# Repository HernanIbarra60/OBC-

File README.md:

# OBC-
This project is an On-Board Computer (OBC) for a CubeSat. Its main core is an STM32F4 microcontroller.

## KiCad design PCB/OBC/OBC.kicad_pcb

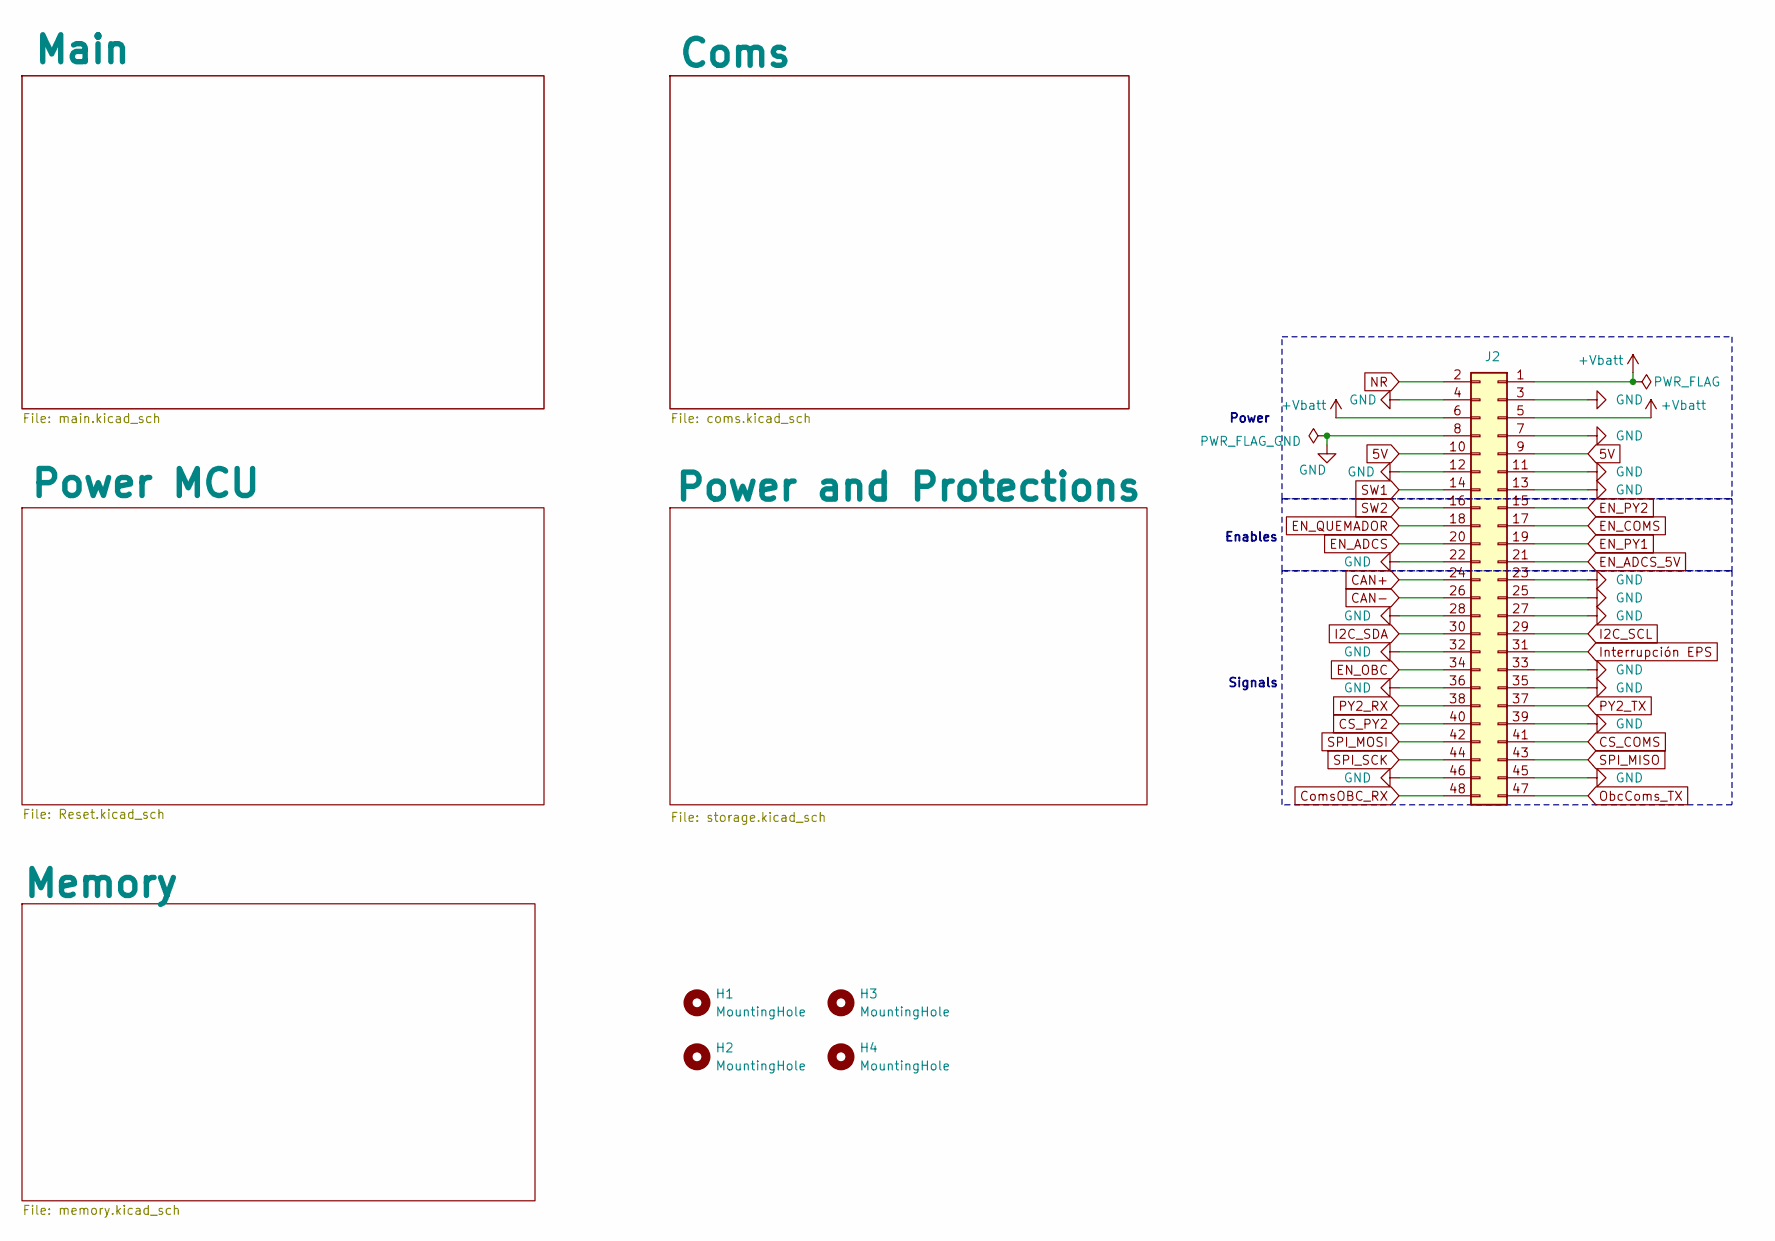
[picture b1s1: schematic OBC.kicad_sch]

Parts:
H1, H2, H3, H4: MountingHole; MountingHole_3.2mm_M3_DIN965_Pad
J2: Conn_02x24_Odd_Even; ESQ-124-Y-X-D

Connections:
5V: J2.9, J2.10
+Vbatt: J2.1, J2.5, J2.6; also elsewhere on the board
CAN+: J2.24; also elsewhere on the board
CAN-: J2.26; also elsewhere on the board
CS_COMS: J2.41; also elsewhere on the board
CS_PY2: J2.40; also elsewhere on the board
ComsOBC_RX: J2.48; also elsewhere on the board
EN_ADCS: J2.20; also elsewhere on the board
EN_ADCS_5V: J2.21; also elsewhere on the board
EN_COMS: J2.17; also elsewhere on the board
EN_OBC: J2.34; also elsewhere on the board
EN_PY1: J2.19; also elsewhere on the board
EN_PY2: J2.15; also elsewhere on the board
EN_QUEMADOR: J2.18; also elsewhere on the board
GND: J2.3, J2.4, J2.7, J2.8, J2.11, J2.12, J2.13, J2.22, J2.23, J2.25, J2.27, J2.28, J2.32, J2.33, J2.35, J2.36, J2.39, J2.45, J2.46; also elsewhere on the board
I2C_SCL: J2.29; also elsewhere on the board
I2C_SDA: J2.30; also elsewhere on the board
Interrupción EPS: J2.31; also elsewhere on the board
NR: J2.2
ObcComs_TX: J2.47; also elsewhere on the board
PY2_RX: J2.38; also elsewhere on the board
PY2_TX: J2.37; also elsewhere on the board
SPI_MISO: J2.43; also elsewhere on the board
SPI_MOSI: J2.42; also elsewhere on the board
SPI_SCK: J2.44; also elsewhere on the board
SW1: J2.14; also elsewhere on the board
SW2: J2.16; also elsewhere on the board

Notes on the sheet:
Signals
Enables
Power

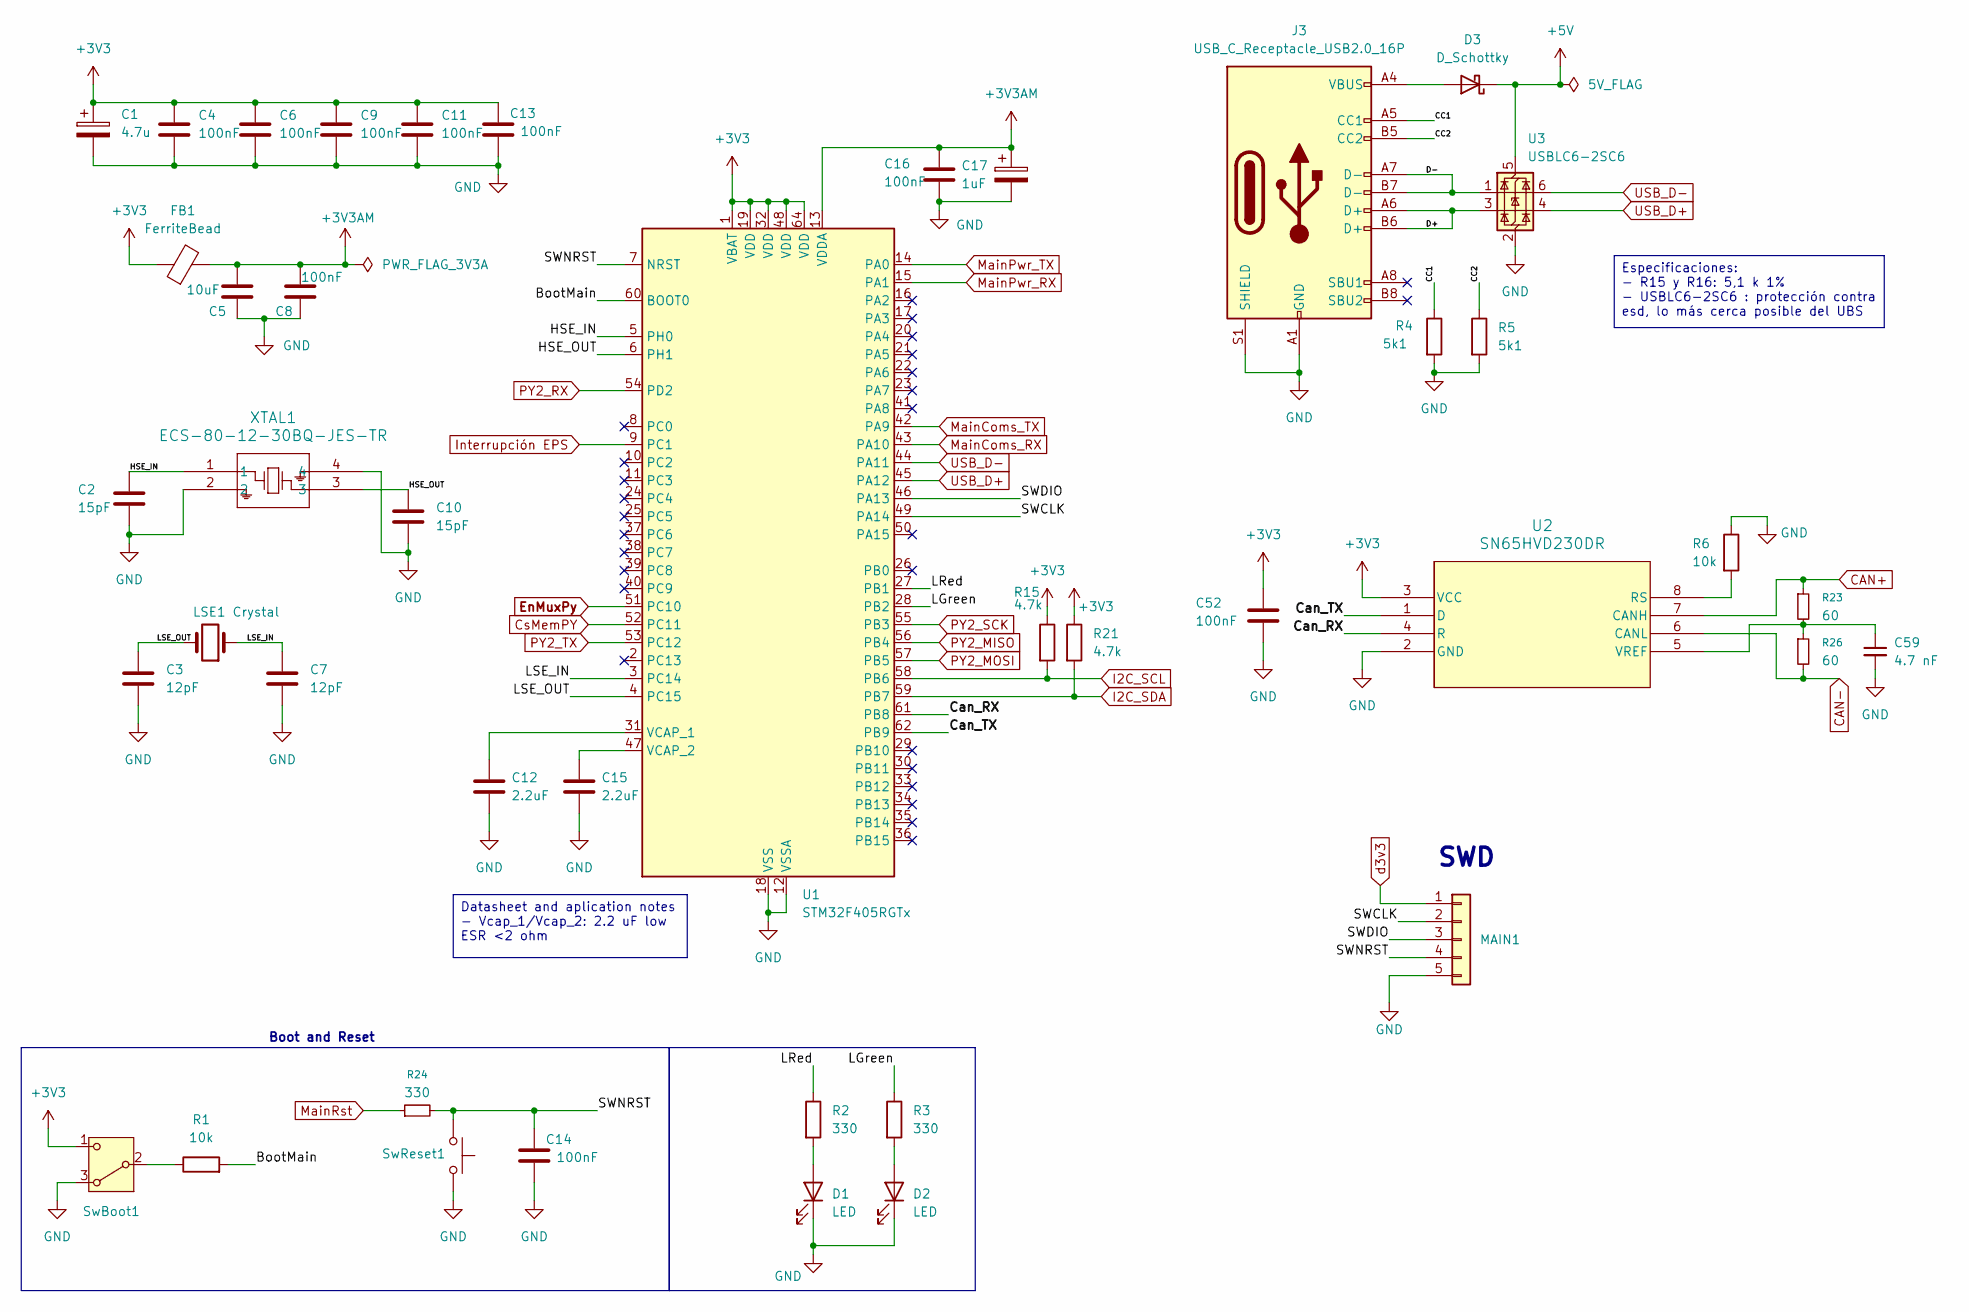
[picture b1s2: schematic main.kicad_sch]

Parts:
C1: 4.7u; C_0805_2012Metric_Pad1.18x1.45mm_HandSolder; LCSC Part Name C98195
C2, C10: 15pF; C_0603_1608Metric_Pad1.08x0.95mm_HandSolder; LCSC Part Name C1644
C3, C7: 12pF; C_0603_1608Metric_Pad1.08x0.95mm_HandSolder; LCSC Part Name C38523
C4, C6, C9, C11, C13, C14, C16, C52: 100nF; C_0603_1608Metric_Pad1.08x0.95mm_HandSolder; LCSC Part Name C15725
C5: 10uF; C_0805_2012Metric_Pad1.18x1.45mm_HandSolder; LCSC Part Name C237493
C8: 100nF; C_0805_2012Metric_Pad1.18x1.45mm_HandSolder; LCSC Part Name C1711
C12, C15: 2.2uF; C_0805_2012Metric_Pad1.18x1.45mm_HandSolder; LCSC Part Name C19110
C17: 1uF; C_0805_2012Metric_Pad1.18x1.45mm_HandSolder; LCSC Part Name C28323
C59: 4.7 nF; C_0805_2012Metric_Pad1.18x1.45mm_HandSolder
D1: LED; LED_0805_2012Metric_Pad1.15x1.40mm_HandSolder; LCSC Part Name C965812
D2: LED; LED_0805_2012Metric_Pad1.15x1.40mm_HandSolder; LCSC Part Name C965815
D3: D_Schottky; D_SOD-323_HandSoldering; LCSC Part Name C124187
FB1: FerriteBead; C_0805_2012Metric_Pad1.18x1.45mm_HandSolder; Mouser 81-BLM21HE601SN1L
J3: USB_C_Receptacle_USB2.0_16P; USB494000A; Mouser 640-USB4940-00-A
LSE1: Crystal; XTAL_NX3215SA_NDK; LCSC Part Name C519280
MAIN1: Conn_01x05; PinHeader_1x05_P2.54mm_Vertical_SMD_Pin1Right; LCSC Part Name C41417362
R1, R6: 10k; R_0805_2012Metric_Pad1.20x1.40mm_HandSolder; LCSC Part Name C2907219
R2, R3: 330; R_0805_2012Metric_Pad1.20x1.40mm_HandSolder; LCSC Part Name C2930157
R4, R5: 5k1; R_0805_2012Metric_Pad1.20x1.40mm_HandSolder; LCSC Part Name C2907269
R15, R21: 4.7k; R_0805_2012Metric_Pad1.20x1.40mm_HandSolder; LCSC Part Name C2907264
R23, R26: 60; R_0603_1608Metric_Pad0.98x0.95mm_HandSolder
R24: 330; R_0805_2012Metric_Pad1.20x1.40mm_HandSolder
SwBoot1: SW_Nidec_CAS-120A1; Nidec_Copal_CAS-120A; LCSC Part Name C22401620
SwReset1: SW_Push; SW_Push_SPST_NO_Alps_SKRK; LCSC Part Name C49234124
U1: STM32F405RGTx; LQFP-64_10x10mm_P0.5mm; LCSC Part Name C15742
U2: SN65HVD230DR; D8; LCSC Part Name C12084
U3: USBLC6-2SC6; SOT-23-6; LCSC Part Name C7519
XTAL1: ECS-80-12-30BQ-JES-TR; ECS-80-12_ECS; Mouser 520-8012-30BQ-JES-TR

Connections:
+3V3: C1.1, C4.1, C6.1, C9.1, C11.1, C13.1, C52.1, FB1.1, R15.1, R21.1, SwBoot1.1 (C), U1.1 (VBAT), U1.19 (VDD), U1.32 (VDD), U1.48 (VDD), U1.64 (VDD), U2.3 (VCC); also elsewhere on the board
+3V3AM: C5.2, C8.2, C16.1, C17.1, FB1.2, U1.13 (VDDA)
+5V: D3.1 (K), U3.5 (VBUS); also elsewhere on the board
/Main/BootMain: R1.2, U1.60 (BOOT0)
/Main/CC1: J3.A5 (CC1), R4.1
/Main/CC2: J3.B5 (CC2), R5.1
/Main/Can_RX: U1.61 (PB8), U2.4 (R)
/Main/Can_TX: U1.62 (PB9), U2.1 (D)
/Main/D+: J3.A6 (D+), J3.B6 (D+), U3.3 (I/O2)
/Main/D-: J3.A7 (D-), J3.B7 (D-), U3.1 (I/O1)
/Main/HSE_IN: C2.1, U1.5 (PH0), XTAL1.1
/Main/HSE_OUT: C10.1, U1.6 (PH1), XTAL1.3
/Main/LGreen: R3.1, U1.28 (PB2)
/Main/LRed: R2.1, U1.27 (PB1)
/Main/LSE_IN: C7.1, LSE1.1, U1.3 (PC14)
/Main/LSE_OUT: C3.1, LSE1.2, U1.4 (PC15)
/Main/SWCLK: MAIN1.2, U1.49 (PA14)
/Main/SWDIO: MAIN1.3, U1.46 (PA13)
/Main/SWNRST: C14.1, MAIN1.4, R24.2, SwReset1.2, U1.7 (NRST)
CAN+: R23.1, U2.7 (CANH); also elsewhere on the board
CAN-: R26.2, U2.6 (CANL); also elsewhere on the board
CsMemPY: U1.52 (PC11); also elsewhere on the board
EnMuxPy: U1.51 (PC10); also elsewhere on the board
GND: C1.2, C2.2, C3.2, C4.2, C5.1, C6.2, C7.2, C8.1, C9.2, C10.2, C11.2, C12.2, C13.2, C14.2, C15.2, C16.2, C17.2, C52.2, C59.2, D1.1 (K), D2.1 (K), J3.A1 (GND), J3.A12 (GND), J3.B1 (GND), J3.B12 (GND), J3.S1 (SHIELD), MAIN1.5, R4.2, R5.2, R6.1, SwBoot1.3 (A), SwReset1.1, U1.12 (VSSA), U1.18 (VSS), U1.63 (VSS), U2.2 (GND), U3.2 (GND), XTAL1.2, XTAL1.4; also elsewhere on the board
I2C_SCL: R15.2, U1.58 (PB6); also elsewhere on the board
I2C_SDA: R21.2, U1.59 (PB7); also elsewhere on the board
Interrupción EPS: U1.9 (PC1); also elsewhere on the board
MainComs_RX: U1.43 (PA10); also elsewhere on the board
MainComs_TX: U1.42 (PA9); also elsewhere on the board
MainPwr_RX: U1.15 (PA1); also elsewhere on the board
MainPwr_TX: U1.14 (PA0); also elsewhere on the board
MainRst: R24.1; also elsewhere on the board
unnamed: D1.2 (A), R2.2
unnamed: D2.2 (A), R3.2
unnamed: D3.2 (A), J3.A4 (VBUS), J3.A9 (VBUS), J3.B4 (VBUS), J3.B9 (VBUS)
unnamed: R1.1, SwBoot1.2 (B)
unnamed: C12.1, U1.31 (VCAP_1)
unnamed: C15.1, U1.47 (VCAP_2)
unnamed: R6.2, U2.8 (RS)
unnamed: C59.1, R23.2, R26.1, U2.5 (VREF)
PY2_MISO: U1.56 (PB4); also elsewhere on the board
PY2_MOSI: U1.57 (PB5); also elsewhere on the board
PY2_RX: U1.54 (PD2); also elsewhere on the board
PY2_SCK: U1.55 (PB3); also elsewhere on the board
PY2_TX: U1.53 (PC12); also elsewhere on the board
USB_D+: U1.45 (PA12), U3.4 (I/O2)
USB_D-: U1.44 (PA11), U3.6 (I/O1)
d3v3: MAIN1.1; also elsewhere on the board

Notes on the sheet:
SWD
Boot and Reset
Datasheet and aplication notes - Vcap_1/Vcap_2: 2.2 uF low ESR <2 ohm
Especificaciones: - R15 y R16: 5,1 k 1% - USBLC6-2SC6 : protección contra esd, lo más cerca posible del UBS

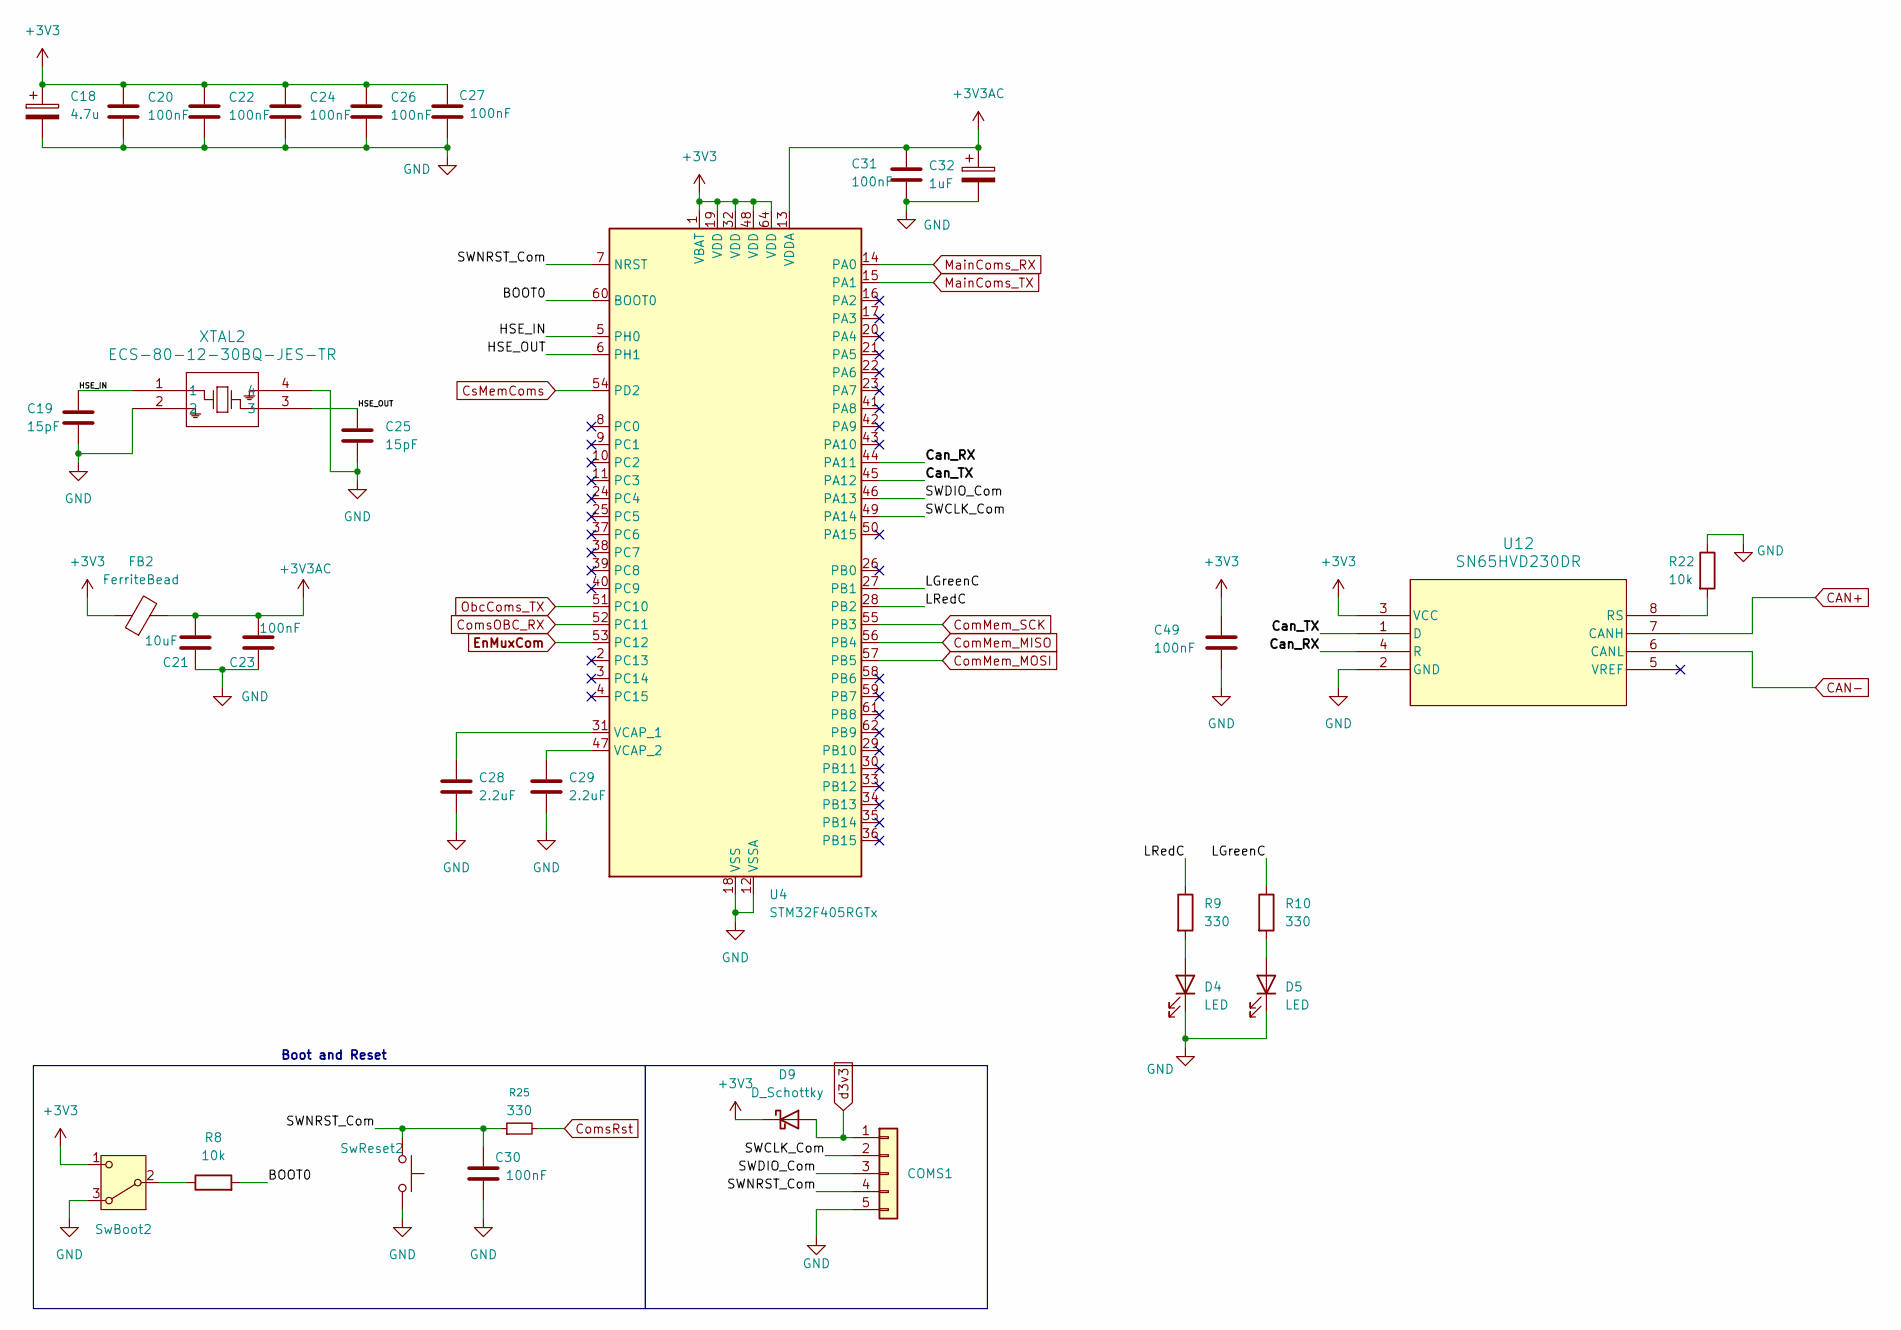
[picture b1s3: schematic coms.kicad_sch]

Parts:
C18: 4.7u; C_0805_2012Metric_Pad1.18x1.45mm_HandSolder; LCSC Part Name C98195
C19, C25: 15pF; C_0603_1608Metric_Pad1.08x0.95mm_HandSolder; LCSC Part Name C1644
C20, C22, C24, C26, C27, C30, C31, C49: 100nF; C_0603_1608Metric_Pad1.08x0.95mm_HandSolder; LCSC Part Name C15725
C21: 10uF; C_0805_2012Metric_Pad1.18x1.45mm_HandSolder; LCSC Part Name C237493
C23: 100nF; C_0805_2012Metric_Pad1.18x1.45mm_HandSolder; LCSC Part Name C1711
C28, C29: 2.2uF; C_0805_2012Metric_Pad1.18x1.45mm_HandSolder; LCSC Part Name C19110
C32: 1uF; C_0805_2012Metric_Pad1.18x1.45mm_HandSolder; LCSC Part Name C28323
COMS1: Conn_01x05; PinHeader_1x05_P2.54mm_Vertical_SMD_Pin1Right; LCSC Part Name C41417362
D4: LED; LED_0805_2012Metric_Pad1.15x1.40mm_HandSolder; LCSC Part Name C965812
D5: LED; LED_0805_2012Metric_Pad1.15x1.40mm_HandSolder; LCSC Part Name C965815
D9: D_Schottky; D_SOD-323_HandSoldering; LCSC Part Name C124187
FB2: FerriteBead; C_0805_2012Metric_Pad1.18x1.45mm_HandSolder; Mouser 81-BLM21HE601SN1L
R8, R22: 10k; R_0805_2012Metric_Pad1.20x1.40mm_HandSolder; LCSC Part Name C2907219
R9, R10: 330; R_0805_2012Metric_Pad1.20x1.40mm_HandSolder; LCSC Part Name C2930157
R25: 330; R_0805_2012Metric_Pad1.20x1.40mm_HandSolder
SwBoot2: SW_Nidec_CAS-120A1; Nidec_Copal_CAS-120A; LCSC Part Name C22401620
SwReset2: SW_Push; SW_Push_SPST_NO_Alps_SKRK; LCSC Part Name C49234124
U4: STM32F405RGTx; LQFP-64_10x10mm_P0.5mm; LCSC Part Name C15742
U12: SN65HVD230DR; D8; LCSC Part Name C12084
XTAL2: ECS-80-12-30BQ-JES-TR; ECS-80-12_ECS; Mouser 520-8012-30BQ-JES-TR

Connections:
+3V3: C18.1, C20.1, C22.1, C24.1, C26.1, C27.1, C49.1, D9.1 (K), FB2.1, SwBoot2.1 (C), U4.1 (VBAT), U4.19 (VDD), U4.32 (VDD), U4.48 (VDD), U4.64 (VDD), U12.3 (VCC); also elsewhere on the board
+3V3AC: C21.2, C23.2, C31.1, C32.1, FB2.2, U4.13 (VDDA)
/Coms/BOOT0: R8.2, U4.60 (BOOT0)
/Coms/Can_RX: U4.44 (PA11), U12.4 (R)
/Coms/Can_TX: U4.45 (PA12), U12.1 (D)
/Coms/HSE_IN: C19.1, U4.5 (PH0), XTAL2.1
/Coms/HSE_OUT: C25.1, U4.6 (PH1), XTAL2.3
/Coms/LGreenC: R10.1, U4.27 (PB1)
/Coms/LRedC: R9.1, U4.28 (PB2)
/Coms/SWCLK_Com: COMS1.2, U4.49 (PA14)
/Coms/SWDIO_Com: COMS1.3, U4.46 (PA13)
/Coms/SWNRST_Com: C30.1, COMS1.4, R25.1, SwReset2.2, U4.7 (NRST)
CAN+: U12.7 (CANH); also elsewhere on the board
CAN-: U12.6 (CANL); also elsewhere on the board
ComMem_MISO: U4.56 (PB4); also elsewhere on the board
ComMem_MOSI: U4.57 (PB5); also elsewhere on the board
ComMem_SCK: U4.55 (PB3); also elsewhere on the board
ComsOBC_RX: U4.52 (PC11); also elsewhere on the board
ComsRst: R25.2; also elsewhere on the board
CsMemComs: U4.54 (PD2); also elsewhere on the board
EnMuxCom: U4.53 (PC12); also elsewhere on the board
GND: C18.2, C19.2, C20.2, C21.1, C22.2, C23.1, C24.2, C25.2, C26.2, C27.2, C28.2, C29.2, C30.2, C31.2, C32.2, C49.2, COMS1.5, D4.1 (K), D5.1 (K), R22.1, SwBoot2.3 (A), SwReset2.1, U4.12 (VSSA), U4.18 (VSS), U4.63 (VSS), U12.2 (GND), XTAL2.2, XTAL2.4; also elsewhere on the board
MainComs_RX: U4.14 (PA0); also elsewhere on the board
MainComs_TX: U4.15 (PA1); also elsewhere on the board
unnamed: D4.2 (A), R9.2
unnamed: D5.2 (A), R10.2
unnamed: R8.1, SwBoot2.2 (B)
unnamed: C28.1, U4.31 (VCAP_1)
unnamed: C29.1, U4.47 (VCAP_2)
unnamed: R22.2, U12.8 (RS)
ObcComs_TX: U4.51 (PC10); also elsewhere on the board
d3v3: COMS1.1, D9.2 (A); also elsewhere on the board

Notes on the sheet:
Boot and Reset

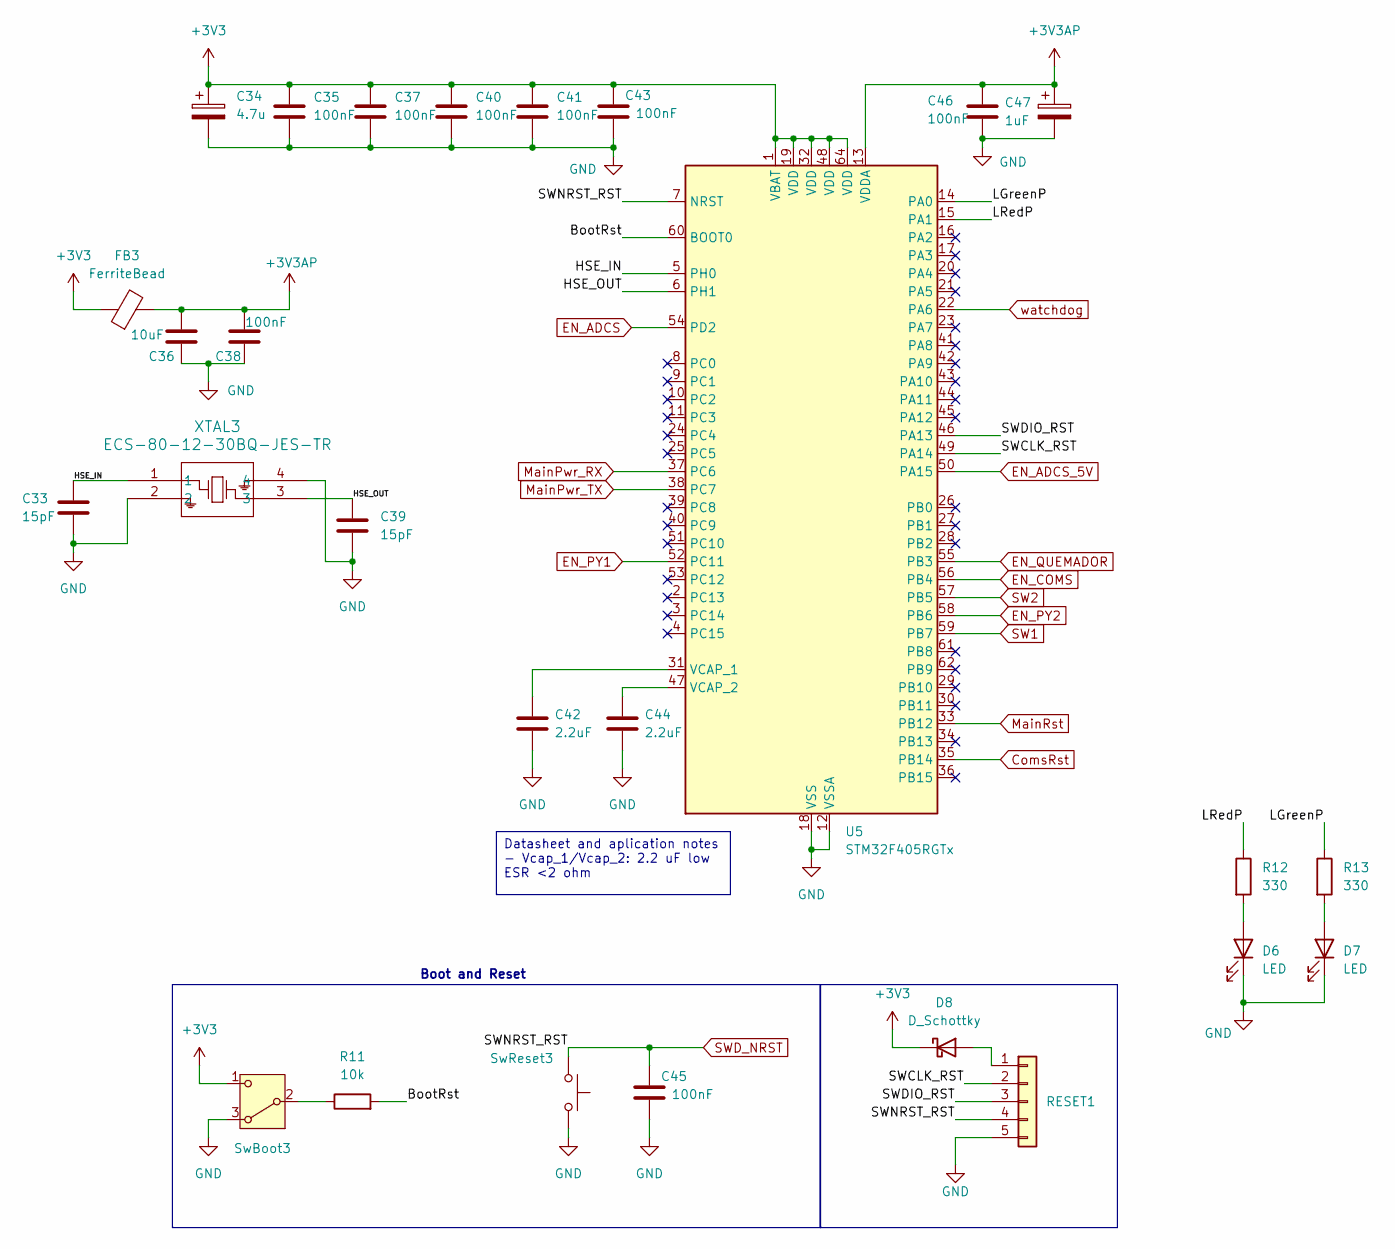
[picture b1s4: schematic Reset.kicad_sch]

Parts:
C33, C39: 15pF; C_0603_1608Metric_Pad1.08x0.95mm_HandSolder; LCSC Part Name C1644
C34: 4.7u; C_0805_2012Metric_Pad1.18x1.45mm_HandSolder; LCSC Part Name C98195
C35, C37, C40, C41, C43, C45, C46: 100nF; C_0603_1608Metric_Pad1.08x0.95mm_HandSolder; LCSC Part Name C15725
C36: 10uF; C_0805_2012Metric_Pad1.18x1.45mm_HandSolder; LCSC Part Name C237493
C38: 100nF; C_0805_2012Metric_Pad1.18x1.45mm_HandSolder; LCSC Part Name C1711
C42, C44: 2.2uF; C_0805_2012Metric_Pad1.18x1.45mm_HandSolder; LCSC Part Name C19110
C47: 1uF; C_0805_2012Metric_Pad1.18x1.45mm_HandSolder; LCSC Part Name C28323
D6: LED; LED_0805_2012Metric_Pad1.15x1.40mm_HandSolder; LCSC Part Name C965812
D7: LED; LED_0805_2012Metric_Pad1.15x1.40mm_HandSolder; LCSC Part Name C965815
D8: D_Schottky; D_SOD-323_HandSoldering; LCSC Part Name C124187
FB3: FerriteBead; C_0805_2012Metric_Pad1.18x1.45mm_HandSolder; Mouser 81-BLM21HE601SN1L
R11: 10k; R_0805_2012Metric_Pad1.20x1.40mm_HandSolder; LCSC Part Name C2907219
R12, R13: 330; R_0805_2012Metric_Pad1.20x1.40mm_HandSolder; LCSC Part Name C2930157
RESET1: Conn_01x05; PinHeader_1x05_P2.54mm_Vertical_SMD_Pin1Right; LCSC Part Name C41417362
SwBoot3: SW_Nidec_CAS-120A1; Nidec_Copal_CAS-120A; LCSC Part Name C22401620
SwReset3: SW_Push; SW_Push_SPST_NO_Alps_SKRK; LCSC Part Name C49234124
U5: STM32F405RGTx; LQFP-64_10x10mm_P0.5mm; LCSC Part Name C15742
XTAL3: ECS-80-12-30BQ-JES-TR; ECS-80-12_ECS; Mouser 520-8012-30BQ-JES-TR

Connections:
+3V3: C34.1, C35.1, C37.1, C40.1, C41.1, C43.1, D8.1 (K), FB3.1, SwBoot3.1 (C), U5.1 (VBAT), U5.19 (VDD), U5.32 (VDD), U5.48 (VDD), U5.64 (VDD); also elsewhere on the board
+3V3AP: C36.2, C38.2, C46.1, C47.1, FB3.2, U5.13 (VDDA)
/Power MCU/BootRst: R11.2, U5.60 (BOOT0)
/Power MCU/HSE_IN: C33.1, U5.5 (PH0), XTAL3.1
/Power MCU/HSE_OUT: C39.1, U5.6 (PH1), XTAL3.3
/Power MCU/LGreenP: R13.1, U5.14 (PA0)
/Power MCU/LRedP: R12.1, U5.15 (PA1)
/Power MCU/SWCLK_RST: RESET1.2, U5.49 (PA14)
/Power MCU/SWDIO_RST: RESET1.3, U5.46 (PA13)
ComsRst: U5.35 (PB14); also elsewhere on the board
EN_ADCS: U5.54 (PD2); also elsewhere on the board
EN_ADCS_5V: U5.50 (PA15); also elsewhere on the board
EN_COMS: U5.56 (PB4); also elsewhere on the board
EN_PY1: U5.52 (PC11); also elsewhere on the board
EN_PY2: U5.58 (PB6); also elsewhere on the board
EN_QUEMADOR: U5.55 (PB3); also elsewhere on the board
GND: C33.2, C34.2, C35.2, C36.1, C37.2, C38.1, C39.2, C40.2, C41.2, C42.2, C43.2, C44.2, C45.2, C46.2, C47.2, D6.1 (K), D7.1 (K), RESET1.5, SwBoot3.3 (A), SwReset3.1, U5.12 (VSSA), U5.18 (VSS), U5.63 (VSS), XTAL3.2, XTAL3.4; also elsewhere on the board
MainPwr_RX: U5.37 (PC6); also elsewhere on the board
MainPwr_TX: U5.38 (PC7); also elsewhere on the board
MainRst: U5.33 (PB12); also elsewhere on the board
unnamed: D6.2 (A), R12.2
unnamed: D7.2 (A), R13.2
unnamed: D8.2 (A), RESET1.1
unnamed: R11.1, SwBoot3.2 (B)
unnamed: C42.1, U5.31 (VCAP_1)
unnamed: C44.1, U5.47 (VCAP_2)
SW1: U5.59 (PB7); also elsewhere on the board
SW2: U5.57 (PB5); also elsewhere on the board
SWD_NRST: C45.1, RESET1.4, SwReset3.2, U5.7 (NRST); also elsewhere on the board
watchdog: U5.22 (PA6); also elsewhere on the board

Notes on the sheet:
Boot and Reset
Datasheet and aplication notes - Vcap_1/Vcap_2: 2.2 uF low ESR <2 ohm

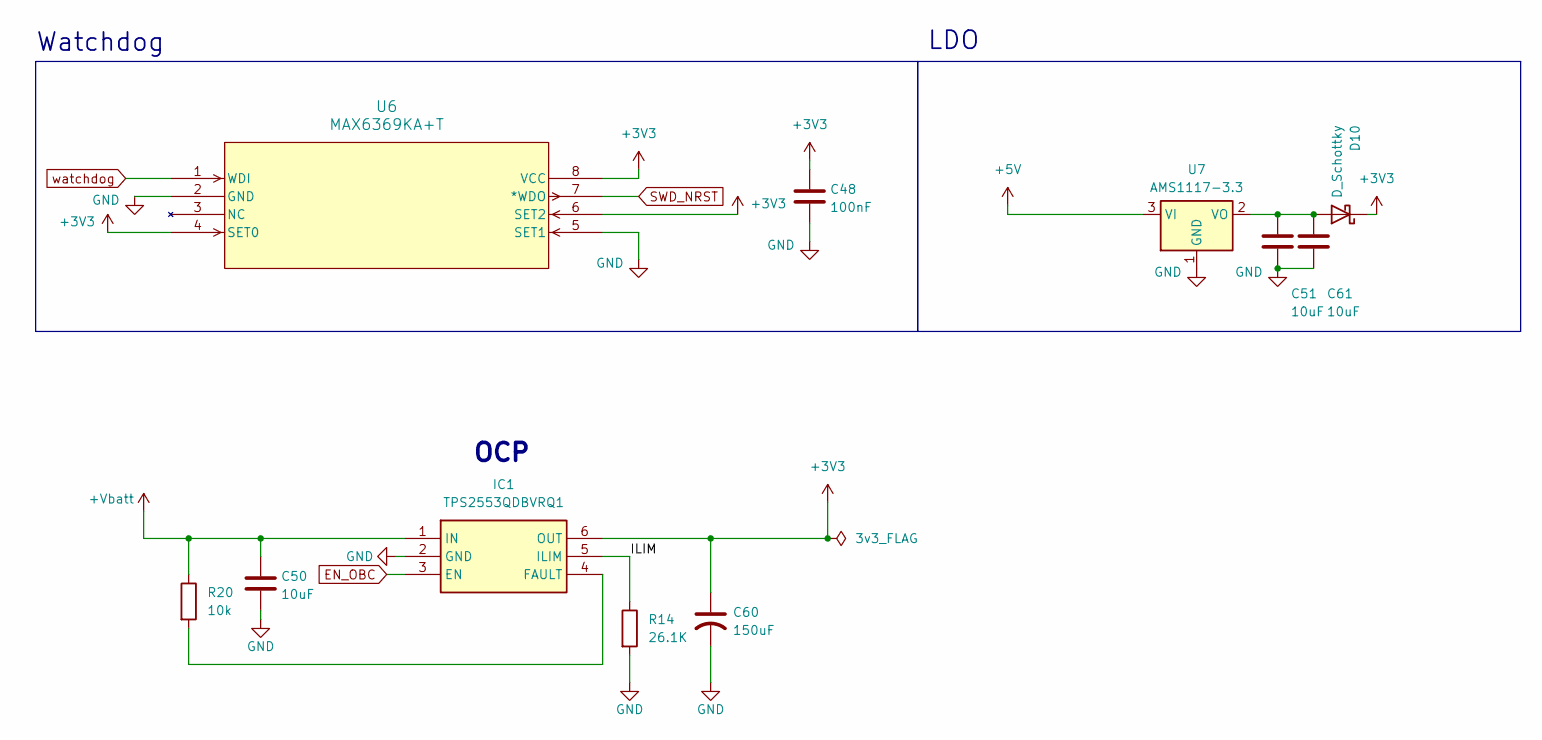
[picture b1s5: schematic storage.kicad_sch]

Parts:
C48: 100nF; C_0805_2012Metric_Pad1.18x1.45mm_HandSolder; LCSC Part Name C1711
C50, C51, C61: 10uF; C_0805_2012Metric_Pad1.18x1.45mm_HandSolder; LCSC Part Name C237493
C60: 150uF; CP_EIA-7343-31_Kemet-D_HandSolder; LCSC Part Name C8025
D10: D_Schottky; D_SOD-323_HandSoldering; LCSC Part Name C124187
IC1: TPS2553QDBVRQ1; SOT95P280X145-6N; Manufacturer_Part_Number TPS2553QDBVRQ1; Mouser Part Number 595-TPS2553QDBVRQ1
R14: 26.1K; R_0805_2012Metric_Pad1.20x1.40mm_HandSolder; LCSC Part Name C2933386
R20: 10k; R_0805_2012Metric_Pad1.20x1.40mm_HandSolder; LCSC Part Name C2907219
U6: MAX6369KA+T; 21-0078H_MXM; LCSC Part Name C128613
U7: AMS1117-3.3; SOT-223-3_TabPin2; LCSC Part Name C6186

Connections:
+3V3: C48.1, C60.1, D10.1 (K), IC1.6 (OUT), U6.4 (SET0), U6.6 (SET2), U6.8 (VCC); also elsewhere on the board
+5V: U7.3 (VI); also elsewhere on the board
+Vbatt: C50.1, IC1.1 (IN), R20.1; also elsewhere on the board
/Power and Protections/ILIM: IC1.5 (ILIM), R14.1
EN_OBC: IC1.3 (EN); also elsewhere on the board
GND: C48.2, C50.2, C51.2, C60.2, C61.2, IC1.2 (GND), R14.2, U6.2 (GND), U6.5 (SET1), U7.1 (GND); also elsewhere on the board
unnamed: C51.1, C61.1, D10.2 (A), U7.2 (VO)
unnamed: IC1.4 (FAULT), R20.2
SWD_NRST: U6.7 (*WDO); also elsewhere on the board
watchdog: U6.1 (WDI); also elsewhere on the board

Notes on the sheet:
Watchdog
OCP
LDO

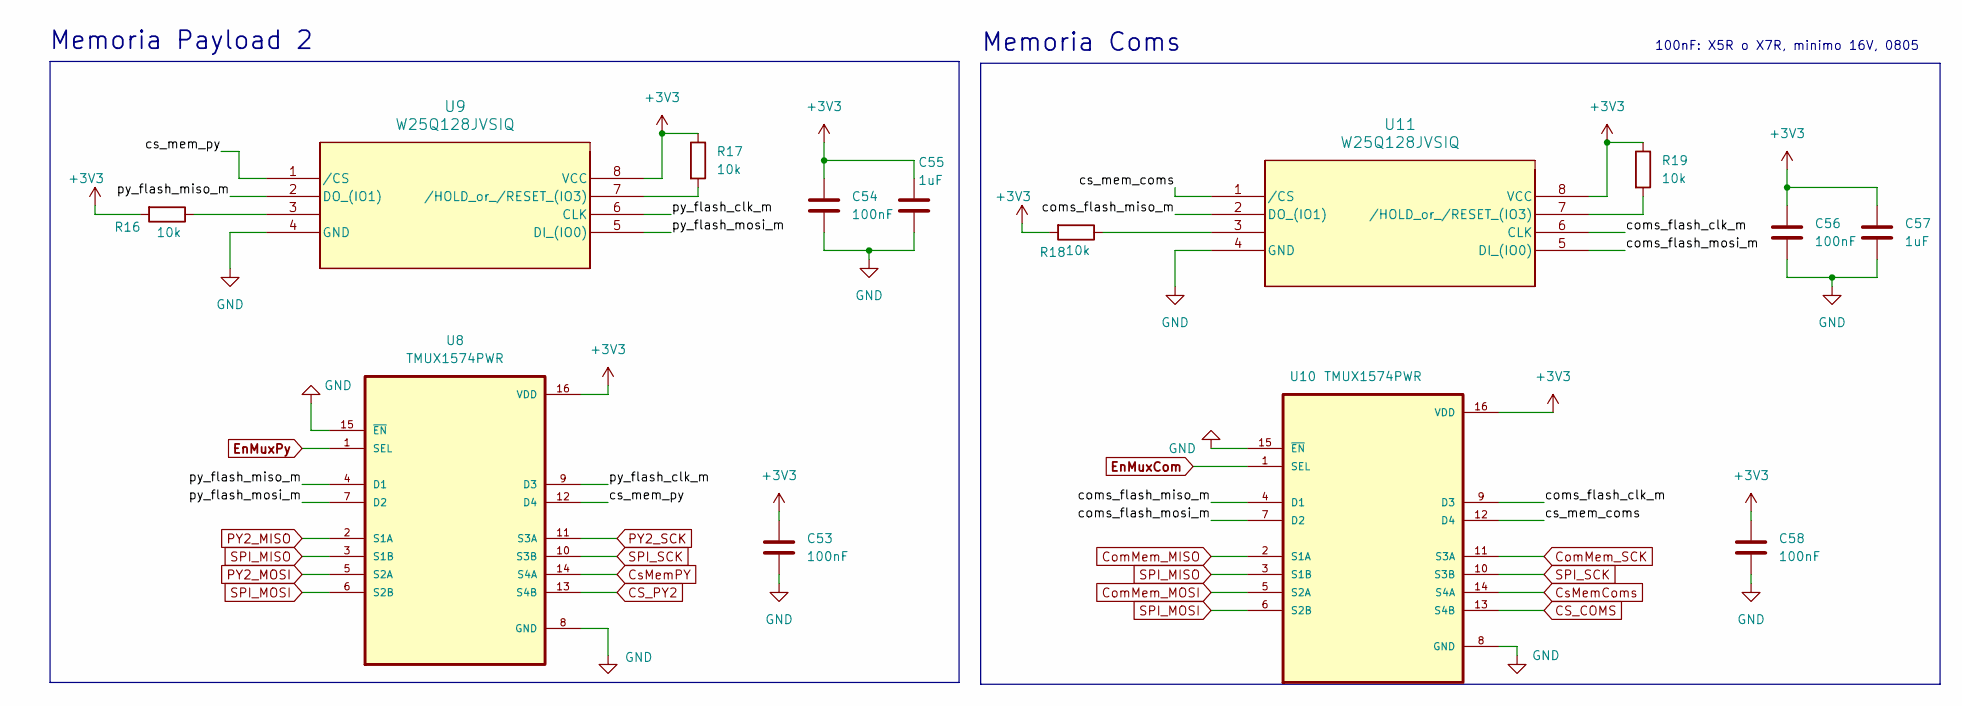
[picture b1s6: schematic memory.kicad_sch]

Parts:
C53, C54, C56, C58: 100nF; C_0805_2012Metric_Pad1.18x1.45mm_HandSolder; LCSC Part Name C1711
C55, C57: 1uF; C_0805_2012Metric_Pad1.18x1.45mm_HandSolder; LCSC Part Name C28323
R16, R17, R18, R19: 10k; R_0805_2012Metric_Pad1.20x1.40mm_HandSolder; LCSC Part Name C2907219
U8, U10: TMUX1574PWR; SOP65P640X120-16N; LCSC Part Name C2673443
U9, U11: W25Q128JVSIQ; SOIC_128JVSIQ_WIN; LCSC Part Name C97521

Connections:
+3V3: C53.1, C54.1, C55.1, C56.1, C57.1, C58.1, R16.2, R17.1, R18.2, R19.1, U8.16 (VDD), U9.8 (VCC), U10.16 (VDD), U11.8 (VCC); also elsewhere on the board
/Memory/coms_flash_clk_m: U10.9 (D3), U11.6 (CLK)
/Memory/coms_flash_miso_m: U10.4 (D1), U11.2 (DO_(IO1))
/Memory/coms_flash_mosi_m: U10.7 (D2), U11.5 (DI_(IO0))
/Memory/cs_mem_coms: U10.12 (D4), U11.1 (/CS)
/Memory/cs_mem_py: U8.12 (D4), U9.1 (/CS)
/Memory/py_flash_clk_m: U8.9 (D3), U9.6 (CLK)
/Memory/py_flash_miso_m: U8.4 (D1), U9.2 (DO_(IO1))
/Memory/py_flash_mosi_m: U8.7 (D2), U9.5 (DI_(IO0))
CS_COMS: U10.13 (S4B); also elsewhere on the board
CS_PY2: U8.13 (S4B); also elsewhere on the board
ComMem_MISO: U10.2 (S1A); also elsewhere on the board
ComMem_MOSI: U10.5 (S2A); also elsewhere on the board
ComMem_SCK: U10.11 (S3A); also elsewhere on the board
CsMemComs: U10.14 (S4A); also elsewhere on the board
CsMemPY: U8.14 (S4A); also elsewhere on the board
EnMuxCom: U10.1 (SEL); also elsewhere on the board
EnMuxPy: U8.1 (SEL); also elsewhere on the board
GND: C53.2, C54.2, C55.2, C56.2, C57.2, C58.2, U8.8 (GND), U8.15 (~EN), U9.4 (GND), U10.8 (GND), U10.15 (~EN), U11.4 (GND); also elsewhere on the board
unnamed: R16.1, U9.3
unnamed: R18.1, U11.3
unnamed: R17.2, U9.7 (/HOLD_or_/RESET_(IO3))
unnamed: R19.2, U11.7 (/HOLD_or_/RESET_(IO3))
PY2_MISO: U8.2 (S1A); also elsewhere on the board
PY2_MOSI: U8.5 (S2A); also elsewhere on the board
PY2_SCK: U8.11 (S3A); also elsewhere on the board
SPI_MISO: U8.3 (S1B), U10.3 (S1B); also elsewhere on the board
SPI_MOSI: U8.6 (S2B), U10.6 (S2B); also elsewhere on the board
SPI_SCK: U8.10 (S3B), U10.10 (S3B); also elsewhere on the board

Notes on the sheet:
Memoria Payload 2
Memoria Coms
100nF: X5R o X7R, minimo 16V, 0805
